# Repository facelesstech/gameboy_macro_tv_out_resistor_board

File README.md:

# gameboy_macro_tv_out_resistor_board
gameboy_macro_tv_out_resistor_board

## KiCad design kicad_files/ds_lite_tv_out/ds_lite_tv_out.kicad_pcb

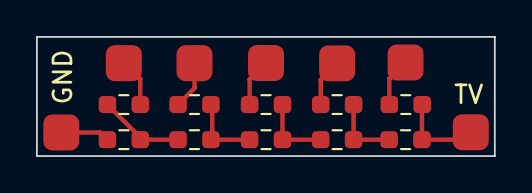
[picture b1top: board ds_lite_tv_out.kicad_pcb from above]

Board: 2 copper layers, 25.4 x 6.6 mm, 17 parts (0 on the bottom side), 11 nets.

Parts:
R1: R470; R_0603_1608Metric_Pad0.98x0.95mm_HandSolder
R2, R4, R6, R8, R10: R 470; R_0603_1608Metric_Pad0.98x0.95mm_HandSolder
R3, R5, R7, R9: R 220; R_0603_1608Metric_Pad0.98x0.95mm_HandSolder
TP1, TP2, TP3, TP4, TP5, TP6, TP7: TestPoint; 2mm_test_point_smd

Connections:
unnamed: R1.2, TP2.1
unnamed: R2.1, TP1.1
unnamed: R1.1, R2.2, R3.1
unnamed: R4.1, TP3.1
unnamed: R3.2, R4.2, R5.1
unnamed: R6.1, TP4.1
unnamed: R5.2, R6.2, R7.1
unnamed: R8.1, TP5.1
unnamed: R7.2, R8.2, R9.1
unnamed: R9.2, R10.2, TP7.1
unnamed: R10.1, TP6.1

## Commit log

2022-12-17 added license
2022-12-17 added kicad files
2022-12-19 updated files
